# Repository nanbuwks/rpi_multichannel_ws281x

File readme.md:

# rpi_multichannel_ws281x

It uses the secondary memory interface (SMI) of the RaspberryPi to generate accurate signals.
The SMI is said to be capable of using 18 channels, but the article only shows 8 or 16 channels. The SMI bus signals are SD0 - SD17 and are assigned to GPIOs 8 - 25.

# Hardware

## origin
fork from
https://github.com/nanbuwks/RFID-RC522_RaspberryPi
(RaspberryPi - RFID - 1602LCD Board)

# Software

## origin
fork from https://github.com/jbentham/rpi

## Some Tips I have looked into this

https://qiita.com/nanbuwks/items/76c6ead17a469b57051b
「RaspberryPi で WS281X LEDストリップをマルチチャンネル駆動する」

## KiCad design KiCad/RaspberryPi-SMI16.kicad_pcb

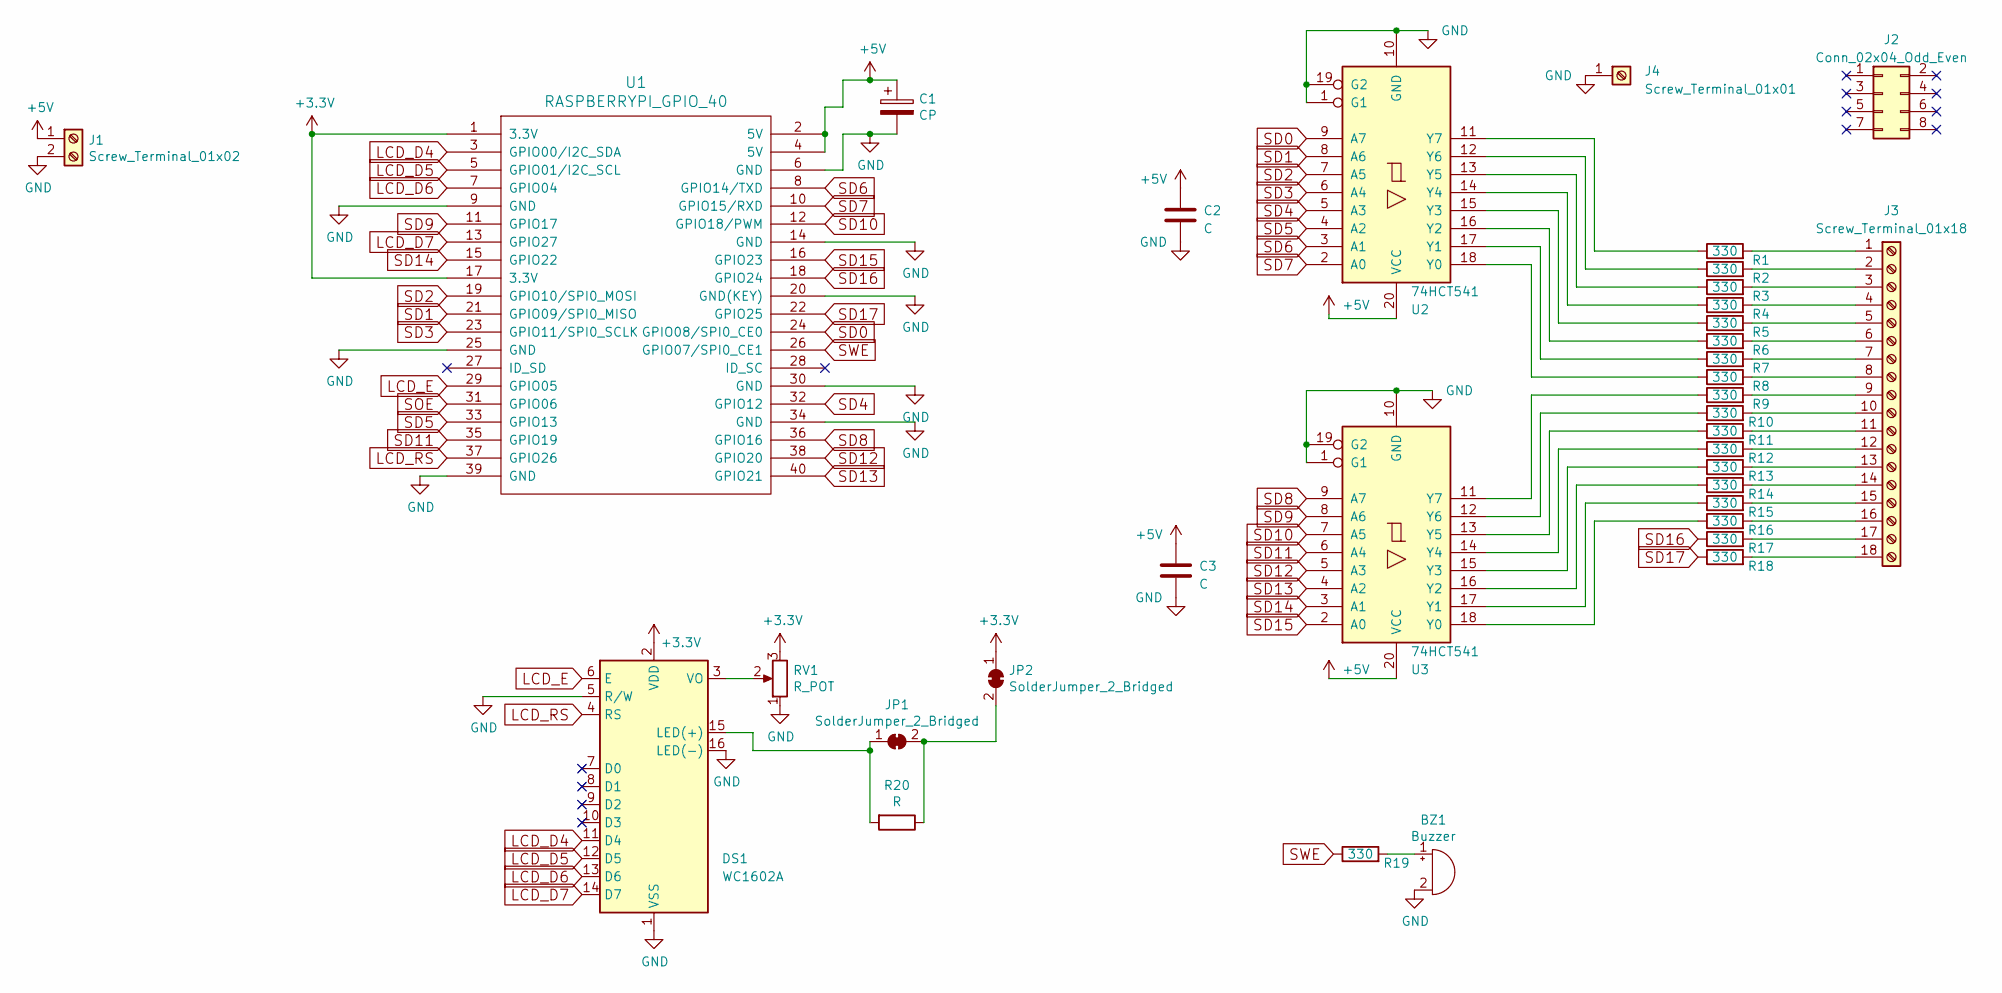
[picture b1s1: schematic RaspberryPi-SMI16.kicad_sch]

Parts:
BZ1: Buzzer; Buzzer_12x9.5RM7.6
C1: CP; CP_Radial_D8.0mm_P3.50mm
C2, C3: C; C_0603_1608Metric
DS1: WC1602A
J1: Screw_Terminal_01x02; TerminalBlock_Phoenix_MKDS-1,5-2_1x02_P5.00mm_Horizontal
J2: Conn_02x04_Odd_Even; MountingHole_3.2mm_M3
J3: Screw_Terminal_01x18; PinHeader_1x18_P2.54mm_Vertical
J4: Screw_Terminal_01x01; PinHeader_1x01_P2.54mm_Vertical
JP1, JP2: SolderJumper_2_Bridged; SolderJumper-2_P1.3mm_Bridged_Pad1.0x1.5mm
R1, R2, R3, R4, R5, R6, R7, R8, R9, R10, R11, R12, R13, R14, R15, R16, R17, R18, R19: 330; R_0603_1608Metric
R20: R; R_Axial_DIN0309_L9.0mm_D3.2mm_P12.70mm_Horizontal
RV1: R_POT; Potentiometer_Runtron_RM-065_Vertical
U1: RASPBERRYPI_GPIO_40; RaspberryPiModelB
U2: 74HCT541; SOIC-20W_7.5x12.8mm_P1.27mm
U3: 74HCT541; SOIC-20W_7.5x15.4mm_P1.27mm

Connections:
+3V3: DS1.2 (VDD), JP2.1 (A), RV1.3, U1.1 (3.3V), U1.17 (3.3V)
+5V: C1.1, C2.1, C3.1, J1.1, U1.2 (5V), U1.4 (5V), U2.20 (VCC), U3.20 (VCC)
GND: BZ1.2 (+), C1.2, C2.2, C3.2, DS1.1 (VSS), DS1.5 (R/W), DS1.16 (LED(-)), J1.2, J4.1, RV1.1, U1.6 (GND), U1.9 (GND), U1.14 (GND), U1.20 (GND(KEY)), U1.25 (GND), U1.30 (GND), U1.34 (GND), U1.39 (GND), U2.1 (G1), U2.10 (GND), U2.19 (G2), U3.1 (G1), U3.10 (GND), U3.19 (G2)
LCD_D4: DS1.11 (D4), U1.3 (GPIO00/I2C_SDA)
LCD_D5: DS1.12 (D5), U1.5 (GPIO01/I2C_SCL)
LCD_D6: DS1.13 (D6), U1.7 (GPIO04)
LCD_D7: DS1.14 (D7), U1.13 (GPIO27)
LCD_E: DS1.6 (E), U1.29 (GPIO05)
LCD_RS: DS1.4 (RS), U1.37 (GPIO26)
unnamed: BZ1.1 (-), R19.2
unnamed: DS1.15 (LED(+)), JP1.1 (A), R20.2
unnamed: DS1.3 (VO), RV1.2
unnamed: J3.1, R1.2
unnamed: J3.2, R2.2
unnamed: J3.3, R3.2
unnamed: J3.4, R4.2
unnamed: J3.5, R5.2
unnamed: J3.6, R6.2
unnamed: J3.7, R7.2
unnamed: J3.8, R8.2
unnamed: J3.9, R9.2
unnamed: J3.10, R10.2
unnamed: J3.11, R11.2
unnamed: J3.12, R12.2
unnamed: J3.13, R13.2
unnamed: J3.14, R14.2
unnamed: J3.15, R15.2
unnamed: J3.16, R16.2
unnamed: J3.17, R17.2
unnamed: J3.18, R18.2
unnamed: JP1.2 (B), JP2.2 (B), R20.1
unnamed: R8.1, U2.18 (Y0)
unnamed: R7.1, U2.17 (Y1)
unnamed: R6.1, U2.16 (Y2)
unnamed: R5.1, U2.15 (Y3)
unnamed: R4.1, U2.14 (Y4)
unnamed: R3.1, U2.13 (Y5)
unnamed: R2.1, U2.12 (Y6)
unnamed: R1.1, U2.11 (Y7)
unnamed: R16.1, U3.18 (Y0)
unnamed: R15.1, U3.17 (Y1)
unnamed: R14.1, U3.16 (Y2)
unnamed: R13.1, U3.15 (Y3)
unnamed: R12.1, U3.14 (Y4)
unnamed: R11.1, U3.13 (Y5)
unnamed: R10.1, U3.12 (Y6)
unnamed: R9.1, U3.11 (Y7)
SD0: U1.24 (GPIO08/SPI0_CE0), U2.9 (A7)
SD1: U1.21 (GPIO09/SPI0_MISO), U2.8 (A6)
SD2: U1.19 (GPIO10/SPI0_MOSI), U2.7 (A5)
SD3: U1.23 (GPIO11/SPI0_SCLK), U2.6 (A4)
SD4: U1.32 (GPIO12), U2.5 (A3)
SD5: U1.33 (GPIO13), U2.4 (A2)
SD6: U1.8 (GPIO14/TXD), U2.3 (A1)
SD7: U1.10 (GPIO15/RXD), U2.2 (A0)
SD8: U1.36 (GPIO16), U3.9 (A7)
SD9: U1.11 (GPIO17), U3.8 (A6)
SD10: U1.12 (GPIO18/PWM), U3.7 (A5)
SD11: U1.35 (GPIO19), U3.6 (A4)
SD12: U1.38 (GPIO20), U3.5 (A3)
SD13: U1.40 (GPIO21), U3.4 (A2)
SD14: U1.15 (GPIO22), U3.3 (A1)
SD15: U1.16 (GPIO23), U3.2 (A0)
SD16: R17.1, U1.18 (GPIO24)
SD17: R18.1, U1.22 (GPIO25)
SOE: U1.31 (GPIO06)
SWE: R19.1, U1.26 (GPIO07/SPI0_CE1)

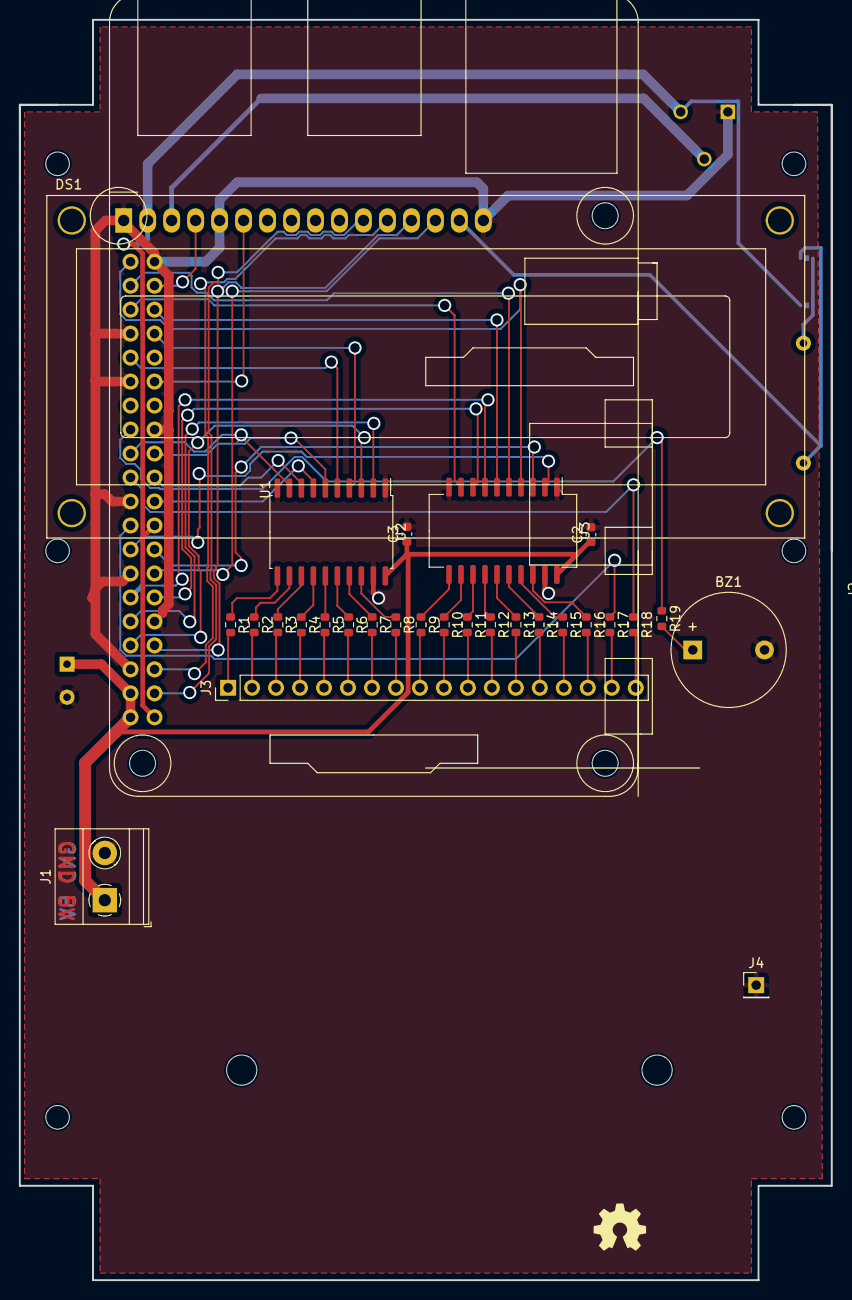
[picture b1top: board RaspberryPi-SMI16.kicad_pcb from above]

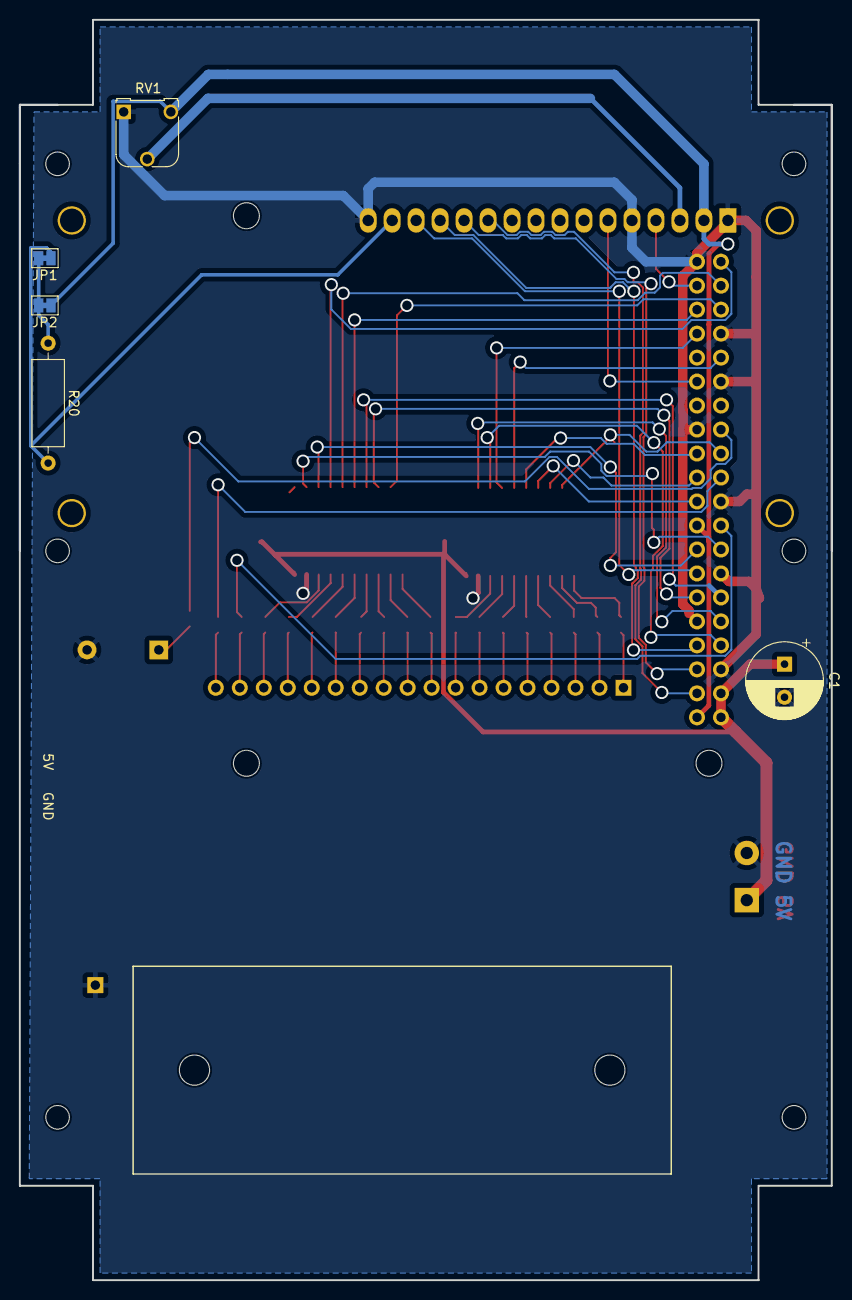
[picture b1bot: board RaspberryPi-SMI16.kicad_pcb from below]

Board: 2 copper layers, 86.0 x 133.5 mm, 36 parts (5 on the bottom side), 66 nets.

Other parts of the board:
OSHW: 1.1; OSHW_LOGL_SYLK_5mm

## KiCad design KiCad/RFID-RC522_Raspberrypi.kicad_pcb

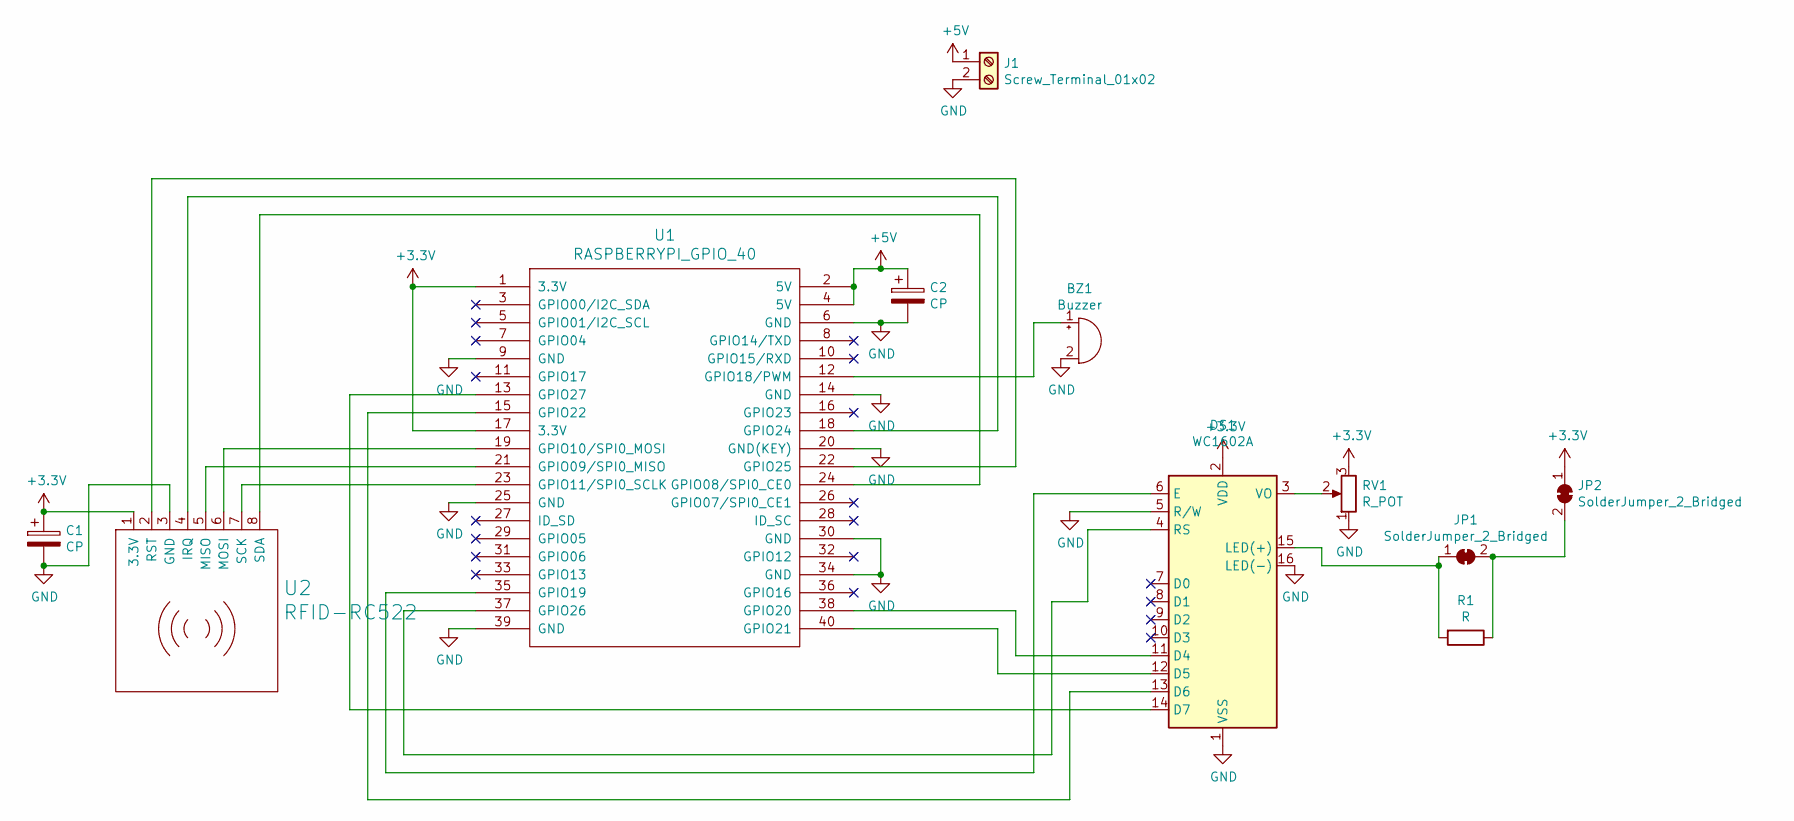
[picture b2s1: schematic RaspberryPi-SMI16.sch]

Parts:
BZ1: Buzzer; Buzzer_12x9.5RM7.6
C1, C2: CP; CP_Radial_D8.0mm_P3.50mm
DS1: WC1602A
J1: Screw_Terminal_01x02; TerminalBlock_bornier-2_P5.08mm
JP1, JP2: SolderJumper_2_Bridged; SolderJumper-2_P1.3mm_Bridged_Pad1.0x1.5mm
R1: R; R_Axial_DIN0309_L9.0mm_D3.2mm_P12.70mm_Horizontal
RV1: R_POT; Potentiometer_Runtron_RM-065_Vertical
U1: RASPBERRYPI_GPIO_40; RaspberryPiModelB
U2: RFID-RC522

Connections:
+3V3: C1.1, DS1.2 (VDD), JP2.1 (A), RV1.3, U1.1 (3.3V), U1.17 (3.3V), U2.1 (3.3V)
+5V: C2.1, J1.1, U1.2 (5V), U1.4 (5V)
GND: BZ1.2 (+), C1.2, C2.2, DS1.1 (VSS), DS1.5 (R/W), DS1.16 (LED(-)), J1.2, RV1.1, U1.6 (GND), U1.9 (GND), U1.14 (GND), U1.20 (GND(KEY)), U1.25 (GND), U1.30 (GND), U1.34 (GND), U1.39 (GND), U2.3 (GND)
unnamed: BZ1.1 (-), U1.12 (GPIO18/PWM)
unnamed: DS1.3 (VO), RV1.2
unnamed: DS1.4 (RS), U1.37 (GPIO26)
unnamed: DS1.6 (E), U1.35 (GPIO19)
unnamed: DS1.11 (D4), U1.38 (GPIO20)
unnamed: DS1.12 (D5), U1.40 (GPIO21)
unnamed: DS1.13 (D6), U1.15 (GPIO22)
unnamed: DS1.14 (D7), U1.13 (GPIO27)
unnamed: DS1.15 (LED(+)), JP1.1 (A), R1.2
unnamed: JP1.2 (B), JP2.2 (B), R1.1
unnamed: U1.18 (GPIO24), U2.4 (IRQ)
unnamed: U1.19 (GPIO10/SPI0_MOSI), U2.6 (MOSI)
unnamed: U1.21 (GPIO09/SPI0_MISO), U2.5 (MISO)
unnamed: U1.22 (GPIO25), U2.2 (RST)
unnamed: U1.23 (GPIO11/SPI0_SCLK), U2.7 (SCK)
unnamed: U1.24 (GPIO08/SPI0_CE0), U2.8 (SDA)

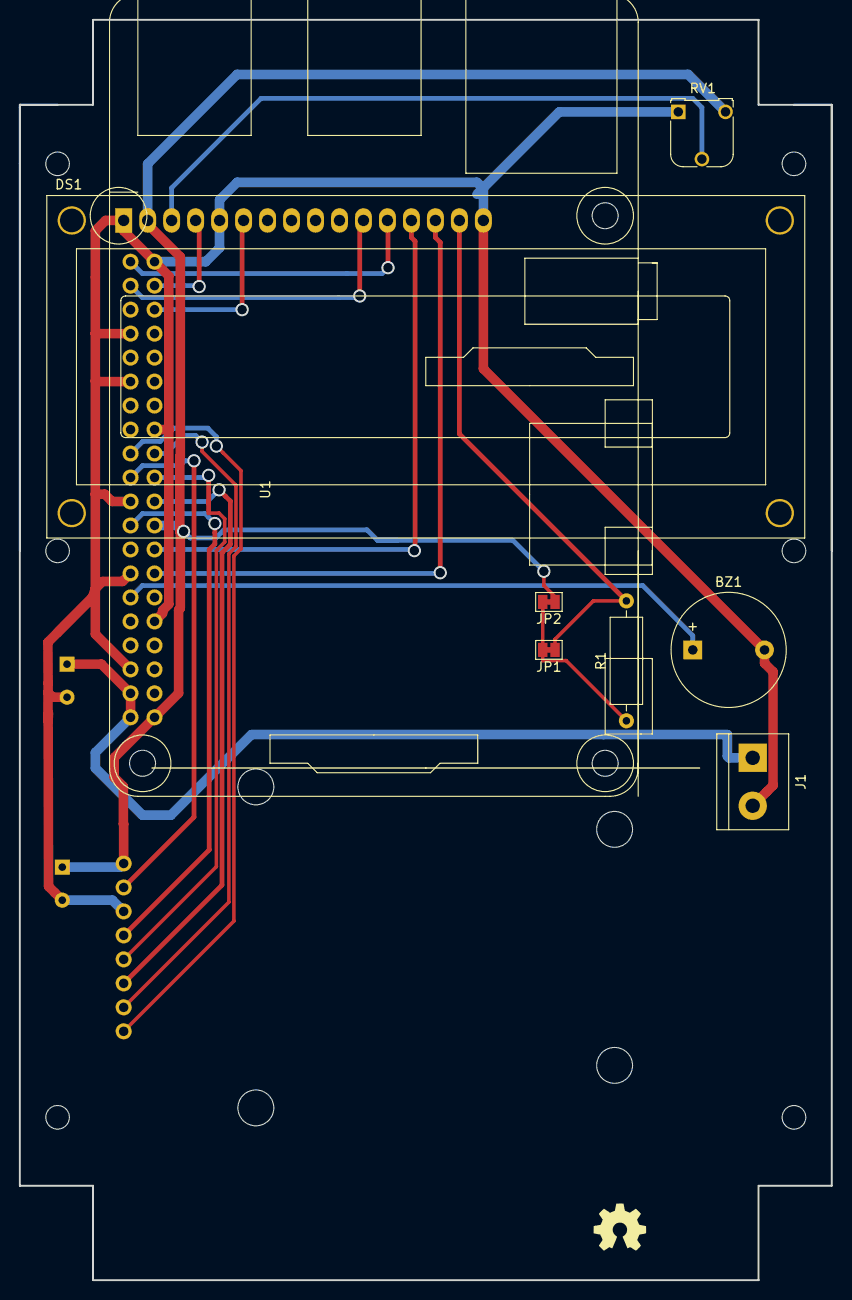
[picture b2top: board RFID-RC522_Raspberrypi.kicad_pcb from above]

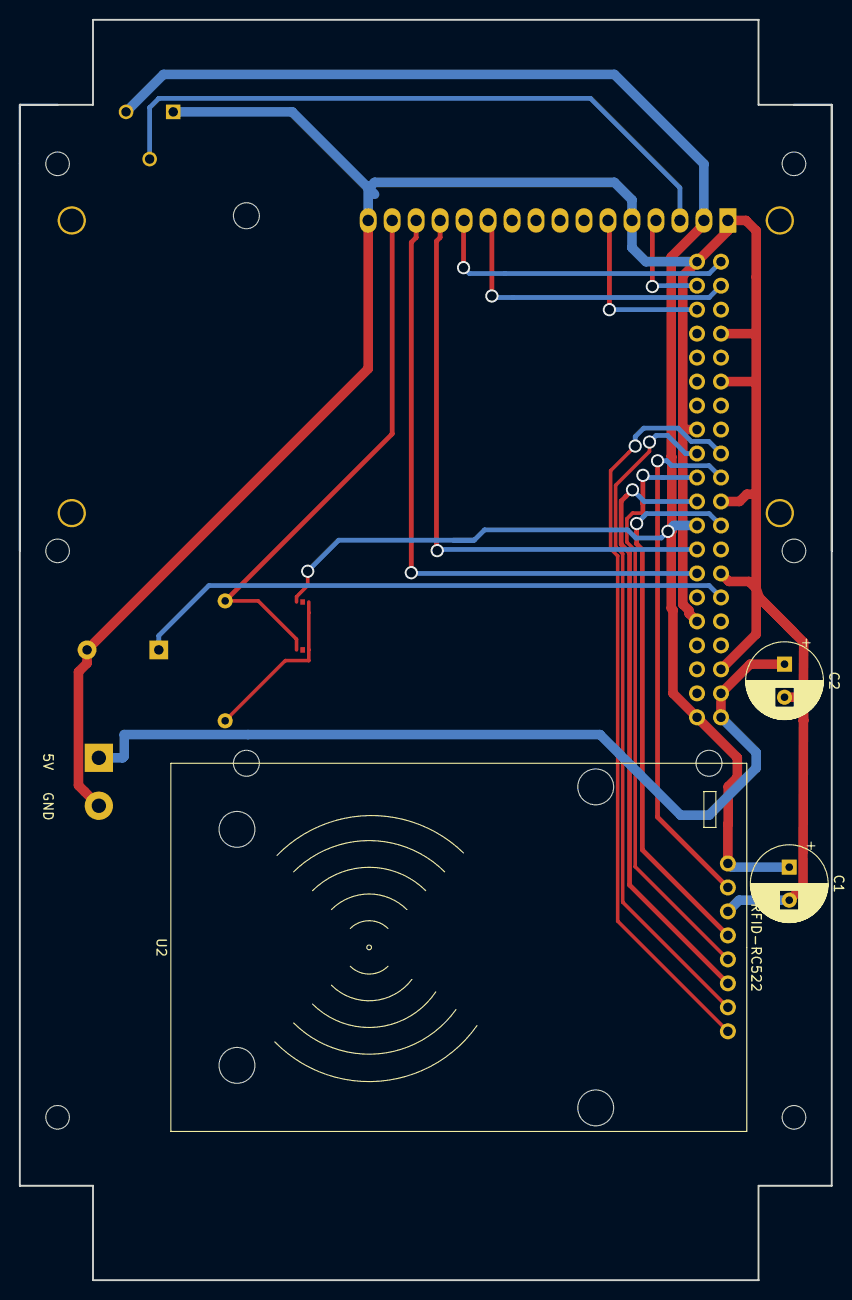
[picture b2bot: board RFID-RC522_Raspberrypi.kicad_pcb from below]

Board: 2 copper layers, 86.0 x 133.5 mm, 12 parts (3 on the bottom side), 19 nets.

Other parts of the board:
OSHW: 1.1; OSHW_LOGL_SYLK_5mm

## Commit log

2023-04-26 add rpi_8chwave.c
2023-04-26 modify readme.md
2023-05-09 mkdir software directory
2023-05-09 add KiCad files.
2023-05-09 modify readme
2023-05-09 rename KiCad files
2023-05-09 change KiCad7
2023-05-10 SMI HAT PCB create
2023-06-25 modify c readme
2023-06-25 wave pattern change / -RBG option add
